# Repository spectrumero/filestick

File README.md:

# FileStick

This is still a very early work in progress.

This project implements an Econet fileserver "onna stick". Acorn had
the FileStore, so this is kind of a play on words on the FileStore.
The system is built on a Lattice UltraPlus 5K FPGA, which includes
128kbyte of static RAM on the chip, as well as a number of dual ported
blockrams, which makes it ideal for a small system project.

The prototype board is based on the UPduino 3.1 board.
See: https://tinyvision.ai/products/upduino-v3-1

The version 1 board contains the econet front end, the up5k FPGA,
an SD card slot, flash memory and a USB interface, implemented with
an FTDI USB UART.

The system consists of a RISC-V core (modified FemtoRV core supporting
some extra CSRs, the ecall instruction to handle system calls, ebreak
and some limited illegal instruction trapping). The core is an rv32imc
(RISC-V 32 bit with the multiply/divide and compressed instructions
extensions).

## Features

* USB powered, < 500mA
* Simple RISC-V implementation and early microcomputer style operating
system. System functions via `ecall` interface.
* Fully buffered econet implementation, with econet exposed via standard
open/read/write/close/ioctl operations.
* Switchable econet clock generation and termination, so that you don't
need a separate clock and terminators for a small Econet.
* Programmable timers.
* USB serial interface with hardware FIFO and hardware CTS/RTS flow control.
Has an interactive mode for use as the system console and raw mode for
transferring files over USB etc.
* FAT support using FatFS for both microSD and built-in flash.
* RGB LED, useful for showing system activity.
* C / C++ programming made easy with newlib and GCC riscv cross compiler,
and a lightweight library and specs file for system-specifics.

## Project structure

* hardware: Contains the Verilog source code. Requires a recent version
of yosys, nextpnr, and the icestorm tools. (Debian users will need to
build these from source, as Debian is still on the old arachnepnr).

* system: Contains the operating system. This isn't a multiuser/
multitasking operating system, it's an OS in the vein of a classic
home micro's operating system. It does provide a number of system
calls using the Linux rv32 syscall numbers. Remember there is no
virtual memory on this very small system, however, some simple memory
protection is planned so that user programs can't accidentally
overwrite kernel memory or device address space.

* lib: The filestick library. This is required for most userspace programs
as at the very least it provides the sbrk implementation needed to properly
support libc's malloc.

## Other programs

(Full disclosure: the emulator and BASIC interpreter below was done with the
full assistance of Claude Code, much as it would be an interesting
project to do them from scratch, it would take me far too long, I had
already been putting off writing the emulator for 2 years :-) )

* emulator: An emulator. See the README file for how to use it. The
emulator is based off the Verilog code and should match it closely.
At the moment it only supports an OS with pseudottys (e.g. Linux) but
it's probably not too hard to do a version for Windows for anyone so
inclined. By default, tries to match the running speed of the real hardware.

* basic: A small BBC BASIC implementation. Implements most of BASIC II
as you would find on a BBC Micro and should be compatible with a saved
BBC BASIC file. Graphics/sound/screen modes not implemented because 
there aren't any. Nor is there an assembler (if you want to write rv32
asm, I suggest using xpack's gnu as). The code segment is around 28k, 
and when running on the board, there's about 33k available for BASIC programs.

* cputest: A test suite for the CPU, checking each unprivileged RV32IMC
instruction against the RISC-V specification. See the README file.

## Toolchain

The xPack GNU RISC-V embedded GCC project is used to build all source
code. xPack provides ready-to-run toolchains for many platforms including
Linux, Windows and MacOS. Other GCC toolchains will probably work, but xPack
is likely the easiest/most convenient to use.

The xPack toolchain includes newlib (the libc).

See their releases here: 
https://github.com/xpack-dev-tools/riscv-none-elf-gcc-xpack/releases

The build system uses cmake. If you're running Linux, your distro almost
certainly has cmake. Otherwise see: https://cmake.org/

## Building

To build the gateware, you will need yosys, nextpnr and icestorm tools installed.
Run:

```
$ cd rtl
$ make PCF=<pcf version of your board>
```

If the PCF variable is left unset, the default will be picked which will be for the
latest version of the hardware.

To build the software, assuming a suitable rv32 compiler (e.g. the xpack one suggested):

```
$ cmake -B build
$ cd build
$ make
```

Outputs will be `build/system/filestick-system.bin`, `build/boot/filestick-boot.bin`,
`build/lib/libfilestick.a`, `build/init/init.elf`.

## Installing

To install the gateware, in the `rtl` directory run `make flash` which will use a
suitable FTDI FT232H programmer to write the flash. This also installs the bootloader
as part of the gateware file.

To install the system image with the FTDI programmer:

```
iceprog -d i:0x0403:0x6014 -X -o 0x020000 build/system/filestick-system.bin
```

To install init with the FTDI programmer:

```
iceprog -d i:0x0403:0x6014 -o 0x030000 build/init/init.elf
```

To install the in-built filesystem:

```
iceprog -d i:0x0403:0x6014 -o 0x040000 256kfs.img
```

(256kfs.img is a blank 256k fat12 filesystem, used for storing system settings
and some basic software).

## TODO

There's much to do. More to come later, including how to write programs
for the FileStick.

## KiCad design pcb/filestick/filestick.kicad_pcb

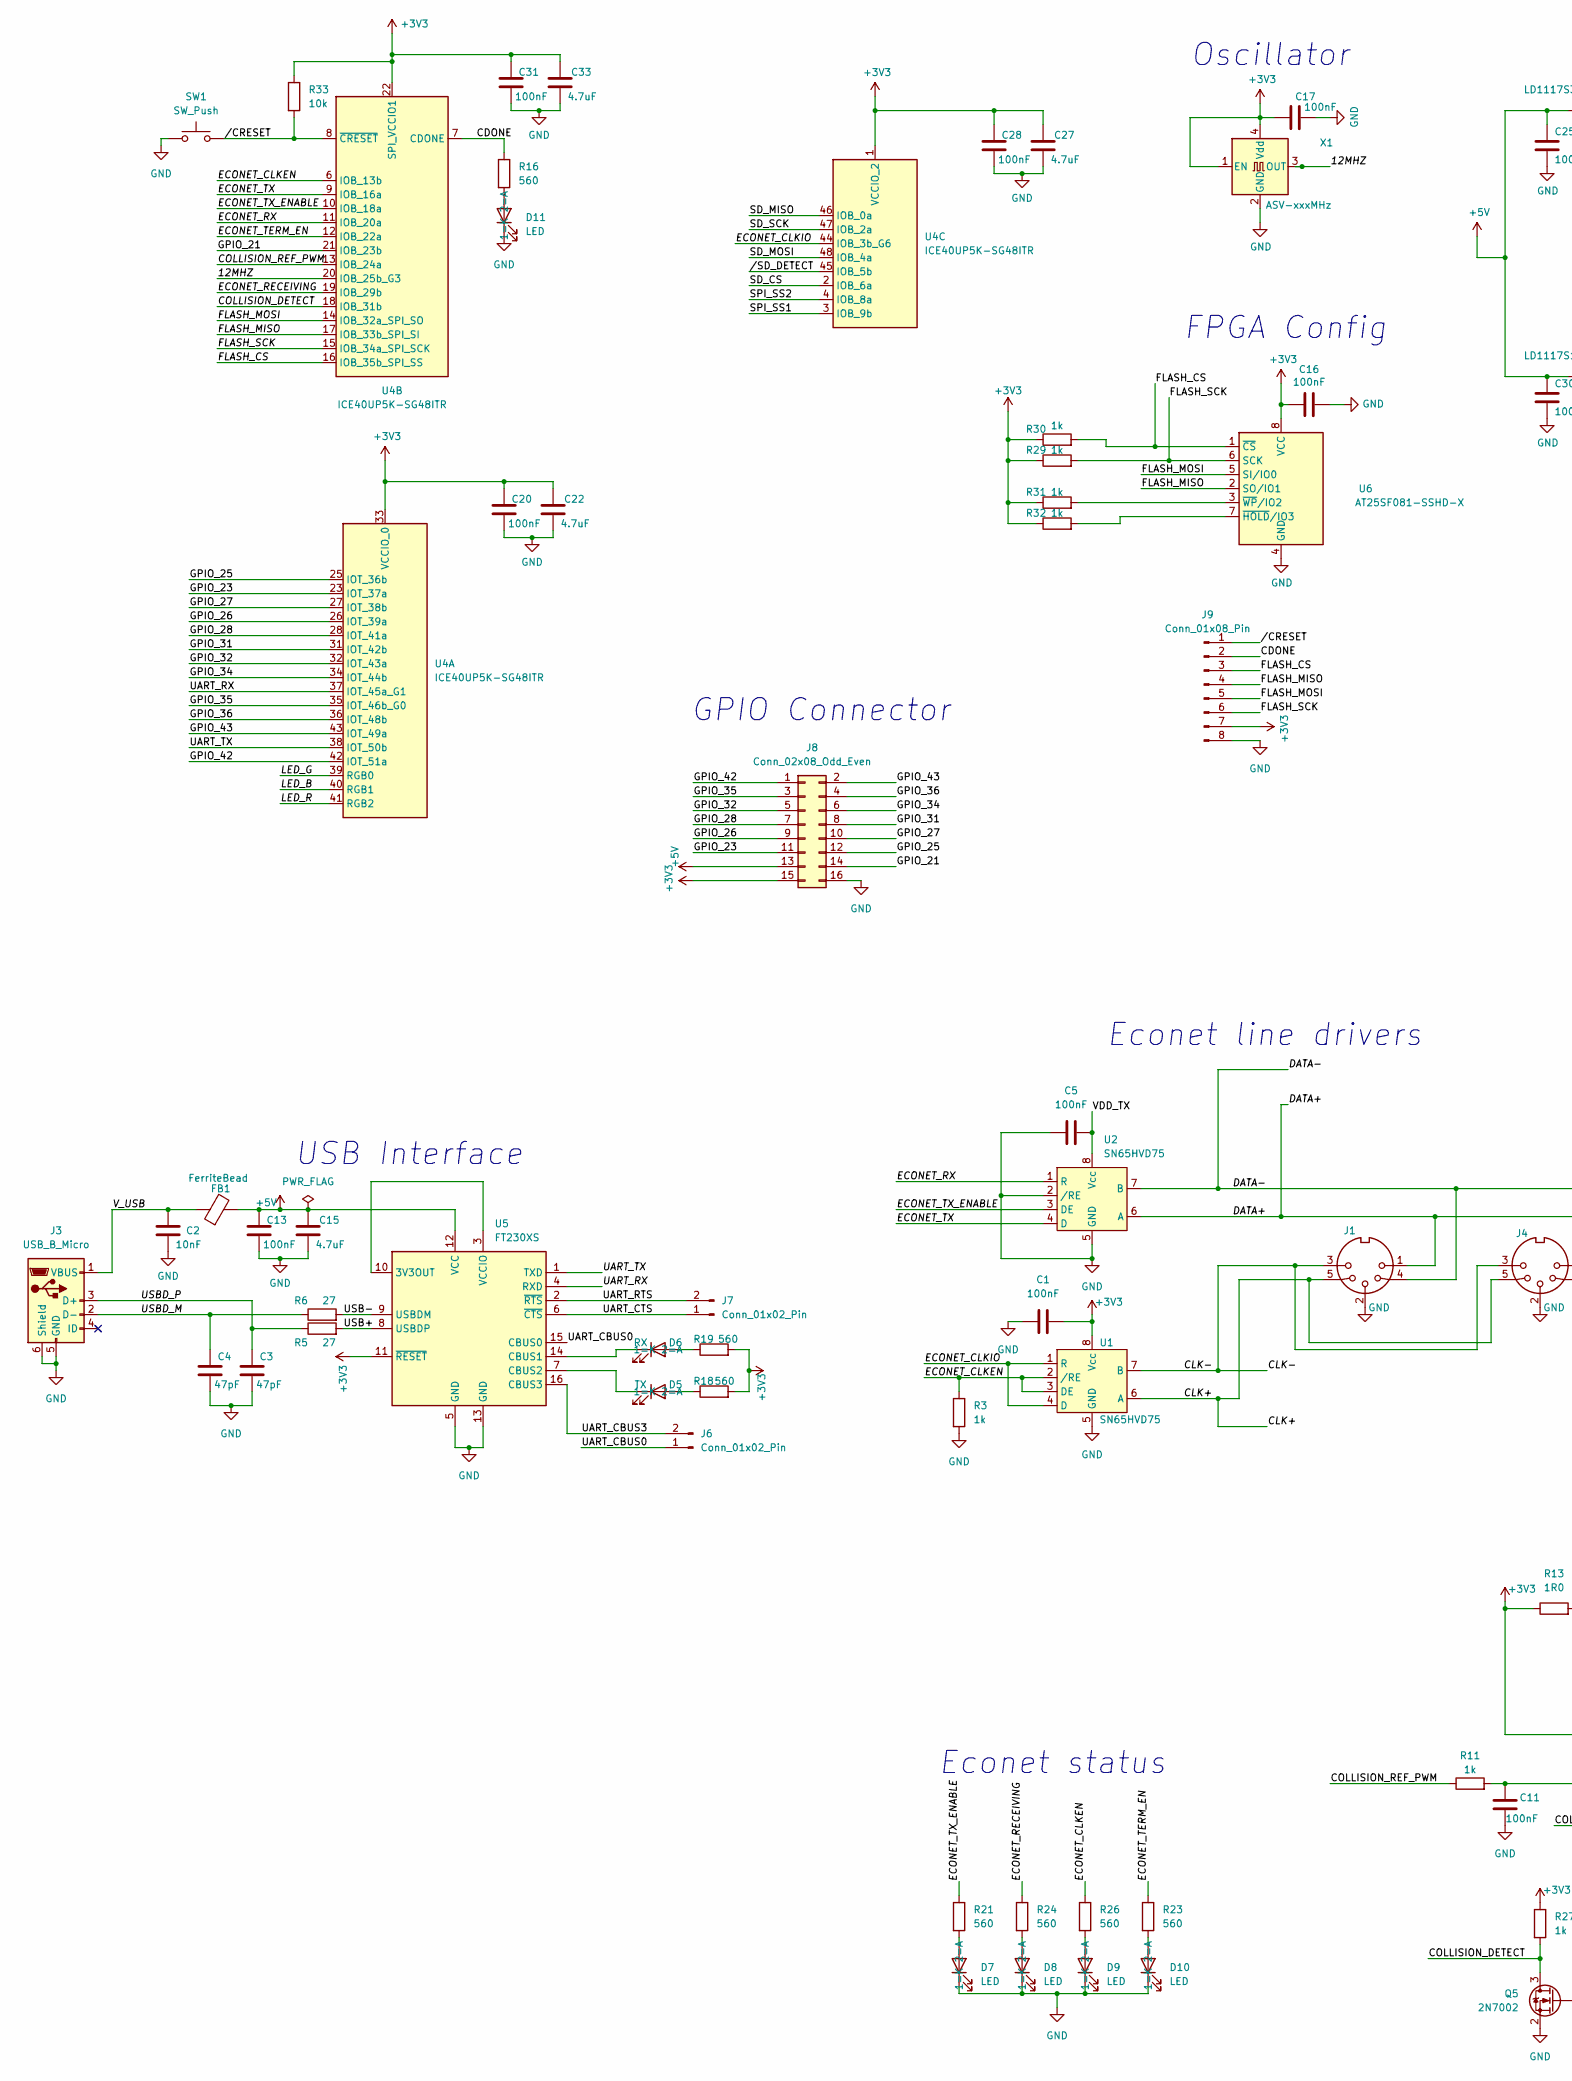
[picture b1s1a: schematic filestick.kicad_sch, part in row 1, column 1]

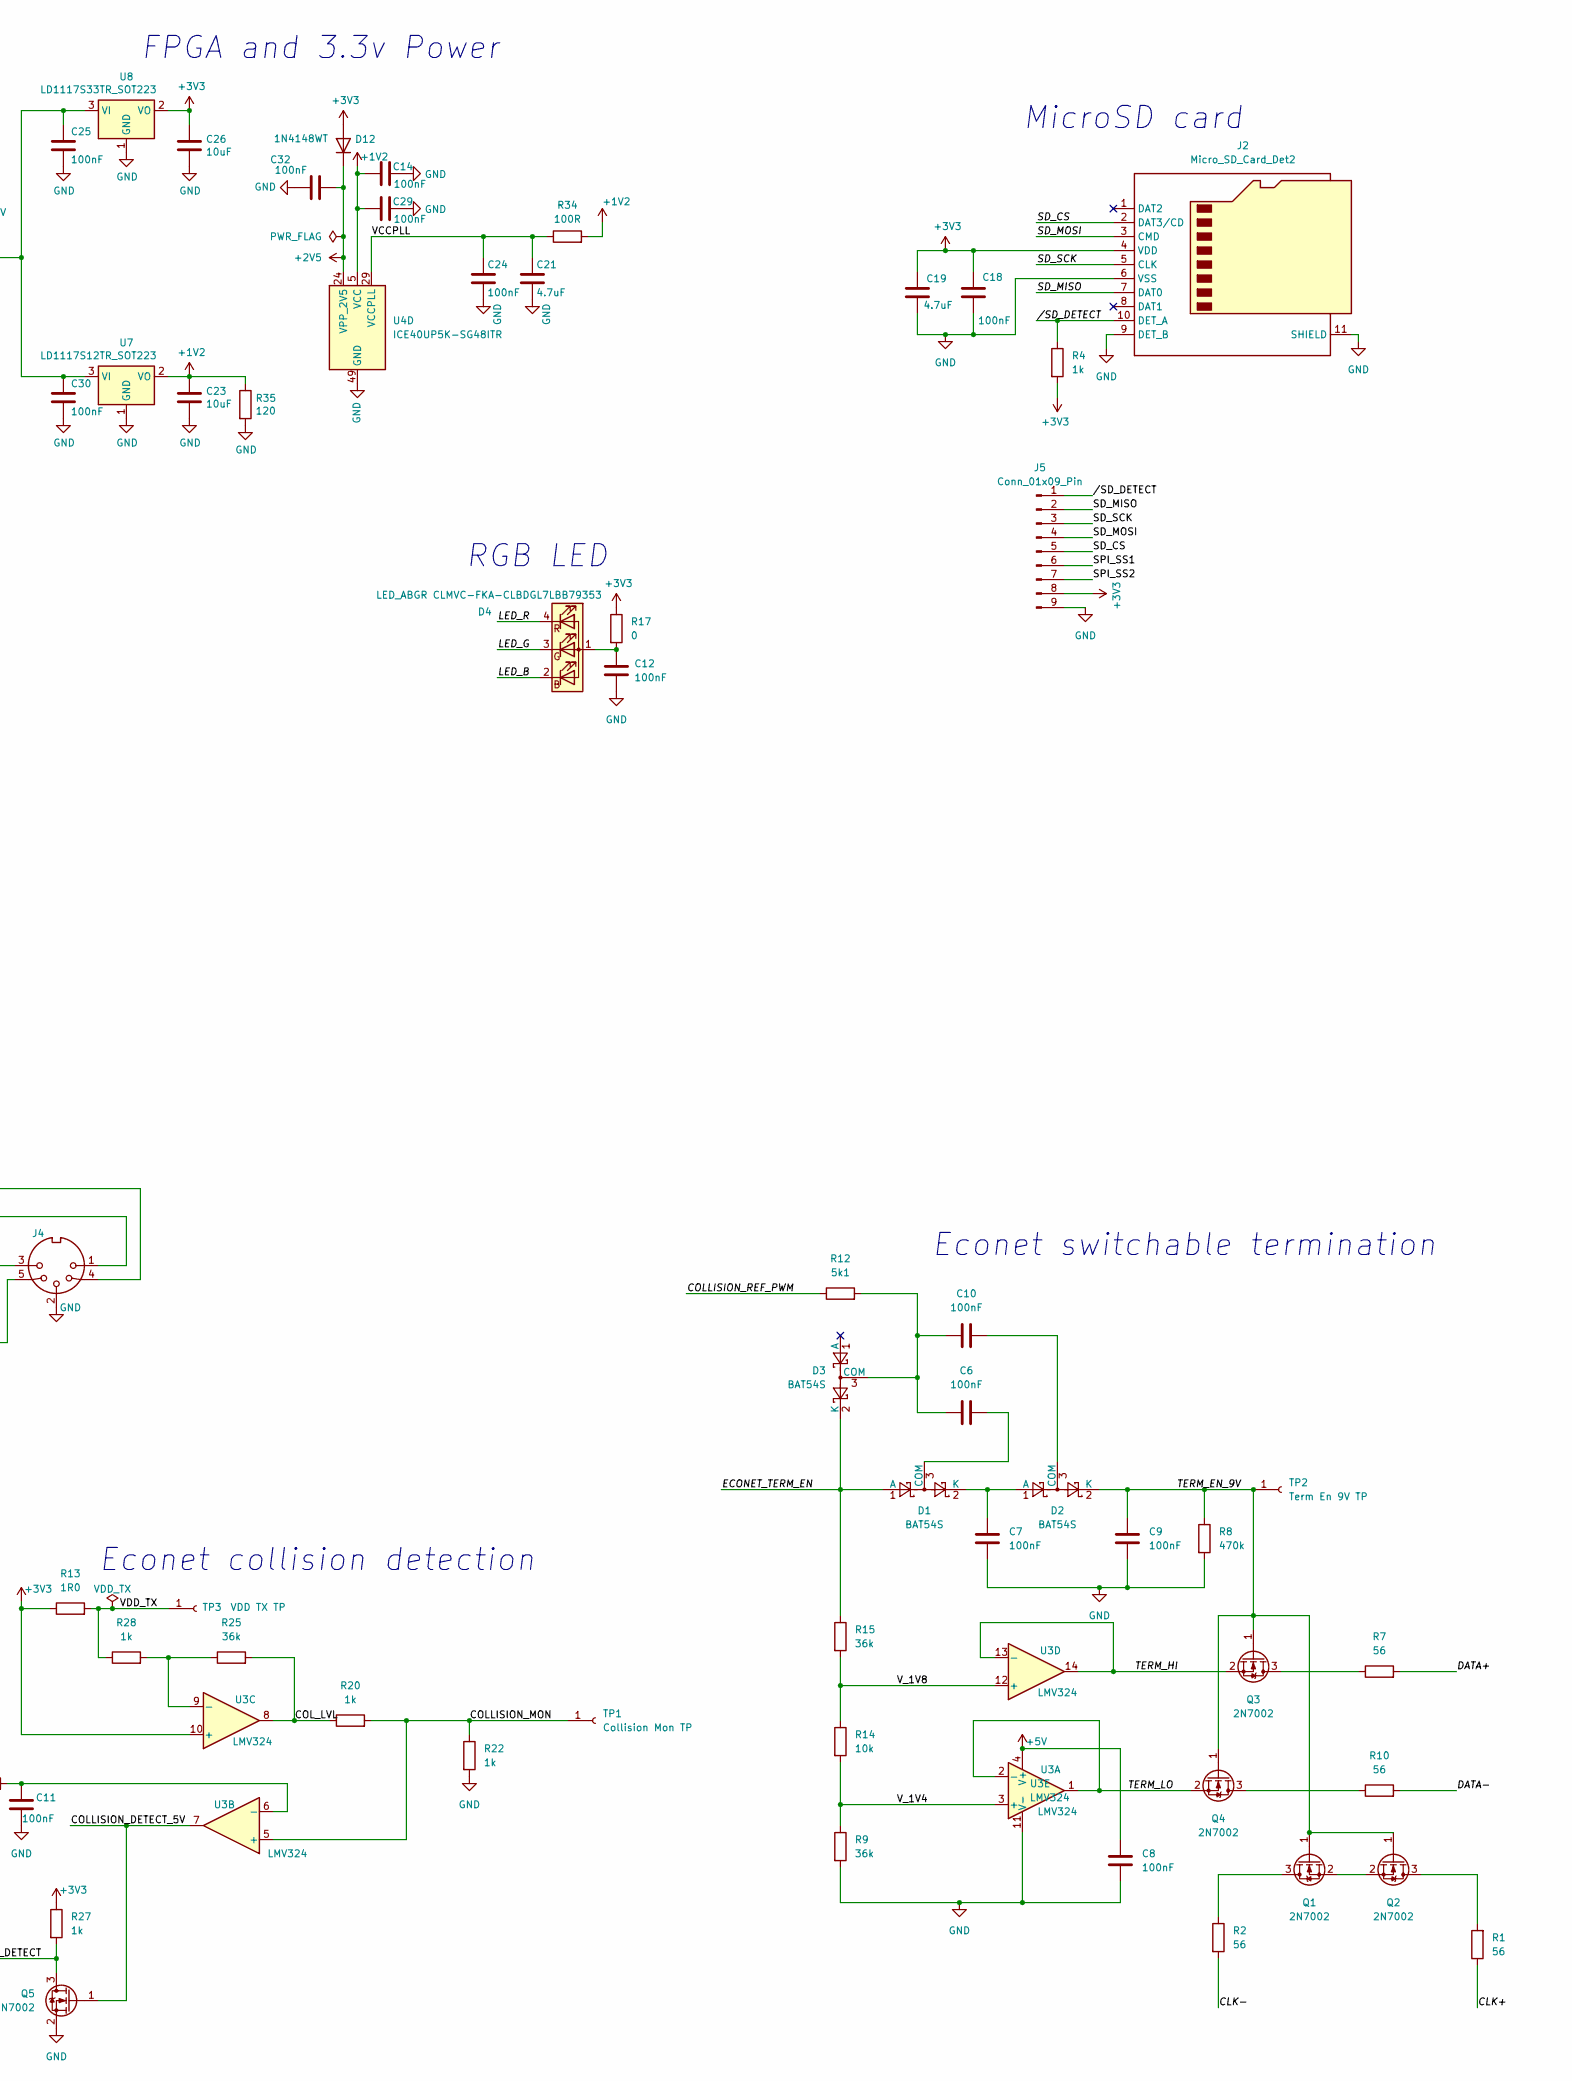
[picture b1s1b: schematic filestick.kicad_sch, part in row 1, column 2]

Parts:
C1, C5, C6, C7, C8, C9, C10, C11, C12, C13, C14, C16, C17, C18, C20, C24, C25, C28, C29, C30, C31, C32: 100nF; C_0603_1608Metric_Pad1.08x0.95mm_HandSolder
C2: 10nF; C_0603_1608Metric_Pad1.08x0.95mm_HandSolder
C3, C4: 47pF; C_0603_1608Metric_Pad1.08x0.95mm_HandSolder
C15, C19, C21, C22, C27, C33: 4.7uF; C_0603_1608Metric_Pad1.08x0.95mm_HandSolder
C23, C26: 10uF; C_0603_1608Metric_Pad1.08x0.95mm_HandSolder
D1, D2, D3: BAT54S; SOT-23
D4: LED_ABGR CLMVC-FKA-CLBDGL7LBB79353; LED_Cree-PLCC4_2x2mm_CW
D5: TX; LED_0603_1608Metric_Pad1.05x0.95mm_HandSolder
D6: RX; LED_0603_1608Metric_Pad1.05x0.95mm_HandSolder
D7, D8, D9, D10, D11: LED; LED_0603_1608Metric_Pad1.05x0.95mm_HandSolder
D12: 1N4148WT; D_SOD-523
FB1: FerriteBead; L_0603_1608Metric_Pad1.05x0.95mm_HandSolder
J1, J4: DIN-5_180degree; Lumberg_DIN41524_5pin
J2: Micro_SD_Card_Det2; microSD_HC_Hirose_DM3D-SF
J3: USB_B_Micro; USB_Micro-B_Molex-105017-0001
J5: Conn_01x09_Pin; PinHeader_1x09_P2.54mm_Vertical
J6, J7: Conn_01x02_Pin; PinHeader_1x02_P2.54mm_Vertical
J8: Conn_02x08_Odd_Even; PinHeader_2x08_P2.54mm_Vertical
J9: Conn_01x08_Pin; PinHeader_1x08_P2.54mm_Vertical
Q1, Q2, Q3, Q4, Q5: 2N7002; SOT-23
R1, R2, R7, R10: 56; R_0603_1608Metric_Pad0.98x0.95mm_HandSolder
R3, R4, R11, R20, R22, R27, R28, R29, R30, R31, R32: 1k; R_0603_1608Metric_Pad0.98x0.95mm_HandSolder
R5, R6: 27; R_0603_1608Metric_Pad0.98x0.95mm_HandSolder
R8: 470k; R_0603_1608Metric_Pad0.98x0.95mm_HandSolder
R9, R15, R25: 36k; R_0603_1608Metric_Pad0.98x0.95mm_HandSolder
R12: 5k1; R_0603_1608Metric_Pad0.98x0.95mm_HandSolder
R13: 1R0; R_0603_1608Metric_Pad0.98x0.95mm_HandSolder
R14, R33: 10k; R_0603_1608Metric_Pad0.98x0.95mm_HandSolder
R16, R18, R19, R21, R23, R24, R26: 560; R_0603_1608Metric_Pad0.98x0.95mm_HandSolder
R17: 0; R_0603_1608Metric_Pad0.98x0.95mm_HandSolder
R34: 100R; R_0603_1608Metric_Pad0.98x0.95mm_HandSolder
R35: 120; R_0603_1608Metric_Pad0.98x0.95mm_HandSolder
SW1: SW_Push; SW_SPST_PTS645
TP1: Collision Mon TP; PinHeader_1x01_P2.54mm_Vertical
TP2: Term En 9V TP; PinHeader_1x01_P2.54mm_Vertical
TP3: VDD TX TP; PinHeader_1x01_P2.54mm_Vertical
U1, U2: SN65HVD75; SOIC-8_5.3x6.2mm_P1.27mm
U3: LMV324; SO-14_5.3x10.2mm_P1.27mm
U4: ICE40UP5K-SG48ITR; QFN-48-1EP_7x7mm_P0.5mm_EP5.6x5.6mm
U5: FT230XS; SSOP-16_3.9x4.9mm_P0.635mm
U6: AT25SF081-SSHD-X; SOIC-8_3.9x4.9mm_P1.27mm
U7: LD1117S12TR_SOT223; SOT-223-3_TabPin2
U8: LD1117S33TR_SOT223; SOT-223-3_TabPin2
X1: ASV-xxxMHz; Oscillator_SMD_Abracon_ASV-4Pin_7.0x5.1mm

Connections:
+1V2: C14.2, C23.1, C29.2, R34.2, R35.1, U4.5 (VCC), U4.30 (VCC), U7.2 (VO)
+2V5: C32.1, D12.1 (K), U4.24 (VPP_2V5)
+3V3: C1.1, C16.1, C17.1, C18.1, C19.1, C20.2, C22.2, C26.1, C27.2, C28.2, C31.2, C33.2, D12.2 (A), J2.4 (VDD), J5.8, J8.15, J9.7, R4.2, R13.1, R17.1, R18.2, R19.2, R27.1, R29.1, R30.1, R31.1, R32.1, R33.1, U1.8 (Vcc), U3.10 (+), U4.1 (VCCIO_2), U4.22 (SPI_VCCIO1), U4.33 (VCCIO_0), U5.11 (~RESET), U6.8 (VCC), U8.2 (VO), X1.1 (EN), X1.4 (Vdd)
+5V: C8.1, C13.2, C15.2, C25.1, C30.1, FB1.2, J8.13, U3.4 (V+), U5.12 (VCC), U7.3 (VI), U8.3 (VI)
/12MHZ: U4.20 (IOB_25b_G3), X1.3 (OUT)
/CDONE: J9.2, R16.1, U4.7 (CDONE)
/CLK+: J1.5, J4.5, R1.1, U1.6 (A)
/CLK-: J1.3, J4.3, R2.2, U1.7 (B)
/COLLISION_DETECT: Q5.3 (D), R27.2, U4.18 (IOB_31b)
/COLLISION_DETECT_5V: Q5.1 (G), U3.7
/COLLISION_MON: R20.2, R22.1, TP1.1, U3.5 (+)
/COLLISION_REF_PWM: R11.1, R12.1, U4.13 (IOB_24a)
/COL_LVL: R20.1, R25.2, U3.8
/DATA+: J1.1, J4.1, R7.2, U2.6 (A)
/DATA-: J1.4, J4.4, R10.2, U2.7 (B)
/ECONET_CLKEN: R3.1, R26.1, U1.2 (/RE), U1.3 (DE), U4.6 (IOB_13b)
/ECONET_CLKIO: U1.1 (R), U1.4 (D), U4.44 (IOB_3b_G6)
/ECONET_RECEIVING: R24.1, U4.19 (IOB_29b)
/ECONET_RX: U2.1 (R), U4.11 (IOB_20a)
/ECONET_TERM_EN: D1.1 (A), D3.2 (K), R15.1, R23.1, U4.12 (IOB_22a)
/ECONET_TX: U2.4 (D), U4.9 (IOB_16a)
/ECONET_TX_ENABLE: R21.1, U2.3 (DE), U4.10 (IOB_18a)
/FLASH_CS: J9.3, R30.2, U4.16 (IOB_35b_SPI_SS), U6.1 (~CS)
/FLASH_MISO: J9.4, U4.17 (IOB_33b_SPI_SI), U6.2 (SO/IO1)
/FLASH_MOSI: J9.5, U4.14 (IOB_32a_SPI_SO), U6.5 (SI/IO0)
/FLASH_SCK: J9.6, R29.2, U4.15 (IOB_34a_SPI_SCK), U6.6 (SCK)
/GPIO_21: J8.14, U4.21 (IOB_23b)
/GPIO_23: J8.11, U4.23 (IOT_37a)
/GPIO_25: J8.12, U4.25 (IOT_36b)
/GPIO_26: J8.9, U4.26 (IOT_39a)
/GPIO_27: J8.10, U4.27 (IOT_38b)
/GPIO_28: J8.7, U4.28 (IOT_41a)
/GPIO_31: J8.8, U4.31 (IOT_42b)
/GPIO_32: J8.5, U4.32 (IOT_43a)
/GPIO_34: J8.6, U4.34 (IOT_44b)
/GPIO_35: J8.3, U4.35 (IOT_46b_G0)
/GPIO_36: J8.4, U4.36 (IOT_48b)
/GPIO_42: J8.1, U4.42 (IOT_51a)
/GPIO_43: J8.2, U4.43 (IOT_49a)
/LED_B: D4.2 (BK), U4.40 (RGB1)
/LED_G: D4.3 (GK), U4.39 (RGB0)
/LED_R: D4.4 (RK), U4.41 (RGB2)
/SD_CS: J2.2 (DAT3/CD), J5.5, U4.2 (IOB_6a)
/SD_MISO: J2.7 (DAT0), J5.2, U4.46 (IOB_0a)
/SD_MOSI: J2.3 (CMD), J5.4, U4.48 (IOB_4a)
/SD_SCK: J2.5 (CLK), J5.3, U4.47 (IOB_2a)
/SPI_SS1: J5.6, U4.3 (IOB_9b)
/SPI_SS2: J5.7, U4.4 (IOB_8a)
/TERM_EN_9V: C9.1, D2.2 (K), Q1.1 (G), Q2.1 (G), Q3.1 (G), Q4.1 (G), R8.1, TP2.1
/TERM_HI: Q3.2 (S), U3.13 (-), U3.14
/TERM_LO: Q4.2 (S), U3.1, U3.2 (-)
/UART_CBUS0: J6.1, U5.15 (CBUS0)
/UART_CBUS3: J6.2, U5.16 (CBUS3)
/UART_CTS: J7.1, U5.6 (~CTS)
/UART_RTS: J7.2, U5.2 (~RTS)
/UART_RX: U4.37 (IOT_45a_G1), U5.4 (RXD)
/UART_TX: U4.38 (IOT_50b), U5.1 (TXD)
/USB+: R5.2, U5.8 (USBDP)
/USB-: R6.2, U5.9 (USBDM)
/USBD_M: C4.1, J3.2 (D-), R6.1
/USBD_P: C3.1, J3.3 (D+), R5.1
/VCCPLL: C21.1, C24.1, R34.1, U4.29 (VCCPLL)
/VDD_TX: C5.2, R13.2, R28.1, TP3.1, U2.8 (Vcc)
/V_1V4: R9.1, R14.2, U3.3 (+)
/V_1V8: R14.1, R15.2, U3.12 (+)
/V_USB: C2.1, FB1.1, J3.1 (VBUS)
//CRESET: J9.1, R33.2, SW1.2, U4.8 (~CRESET)
//SD_DETECT: J2.10 (DET_A), J5.1, R4.1, U4.45 (IOB_5b)
GND: C1.2, C2.2, C3.2, C4.2, C5.1, C7.2, C8.2, C9.2, C11.2, C12.2, C13.1, C14.1, C15.1, C16.2, C17.2, C18.2, C19.2, C20.1, C21.2, C22.1, C23.2, C24.2, C25.2, C26.2, C27.1, C28.1, C29.1, C30.2, C31.1, C32.2, C33.1, D7.1 (K), D8.1 (K), D9.1 (K), D10.1 (K), D11.1 (K), J1.2, J2.6 (VSS), J2.9 (DET_B), J2.11 (SHIELD), J3.5 (GND), J3.6 (Shield), J4.2, J5.9, J8.16, J9.8, Q5.2 (S), R3.2, R8.2, R9.2, R22.2, R35.2, SW1.1, U1.5 (GND), U2.2 (/RE), U2.5 (GND), U3.11 (V-), U4.49 (GND), U5.5 (GND), U5.13 (GND), U6.4 (GND), U7.1 (GND), U8.1 (GND), X1.2 (GND)
unnamed: C6.2, D1.3 (COM)
unnamed: C7.1, D1.2 (K), D2.1 (A)
unnamed: C10.2, D2.3 (COM)
unnamed: C6.1, C10.1, D3.3 (COM), R12.2
unnamed: C12.1, D4.1 (A), R17.2
unnamed: D5.2 (A), R18.1
unnamed: D5.1 (K), U5.7 (CBUS2)
unnamed: D6.2 (A), R19.1
unnamed: D6.1 (K), U5.14 (CBUS1)
unnamed: D7.2 (A), R21.2
unnamed: D8.2 (A), R24.2
unnamed: D9.2 (A), R26.2
unnamed: D10.2 (A), R23.2
unnamed: D11.2 (A), R16.2
unnamed: Q1.3 (D), R2.1
unnamed: Q1.2 (S), Q2.2 (S)
unnamed: Q2.3 (D), R1.2
unnamed: Q3.3 (D), R7.1
unnamed: Q4.3 (D), R10.1
unnamed: C11.1, R11.2, U3.6 (-)
unnamed: R25.1, R28.2, U3.9 (-)
unnamed: U5.3 (VCCIO), U5.10 (3V3OUT)
unnamed: R32.2, U6.7 (~HOLD/IO3)
unnamed: R31.2, U6.3 (~WP/IO2)

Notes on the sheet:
GPIO Connector
MicroSD card
Econet switchable termination
RGB LED
FPGA and 3.3v Power
Econet status
Econet line drivers
Oscillator
FPGA Config
USB Interface
Econet collision detection

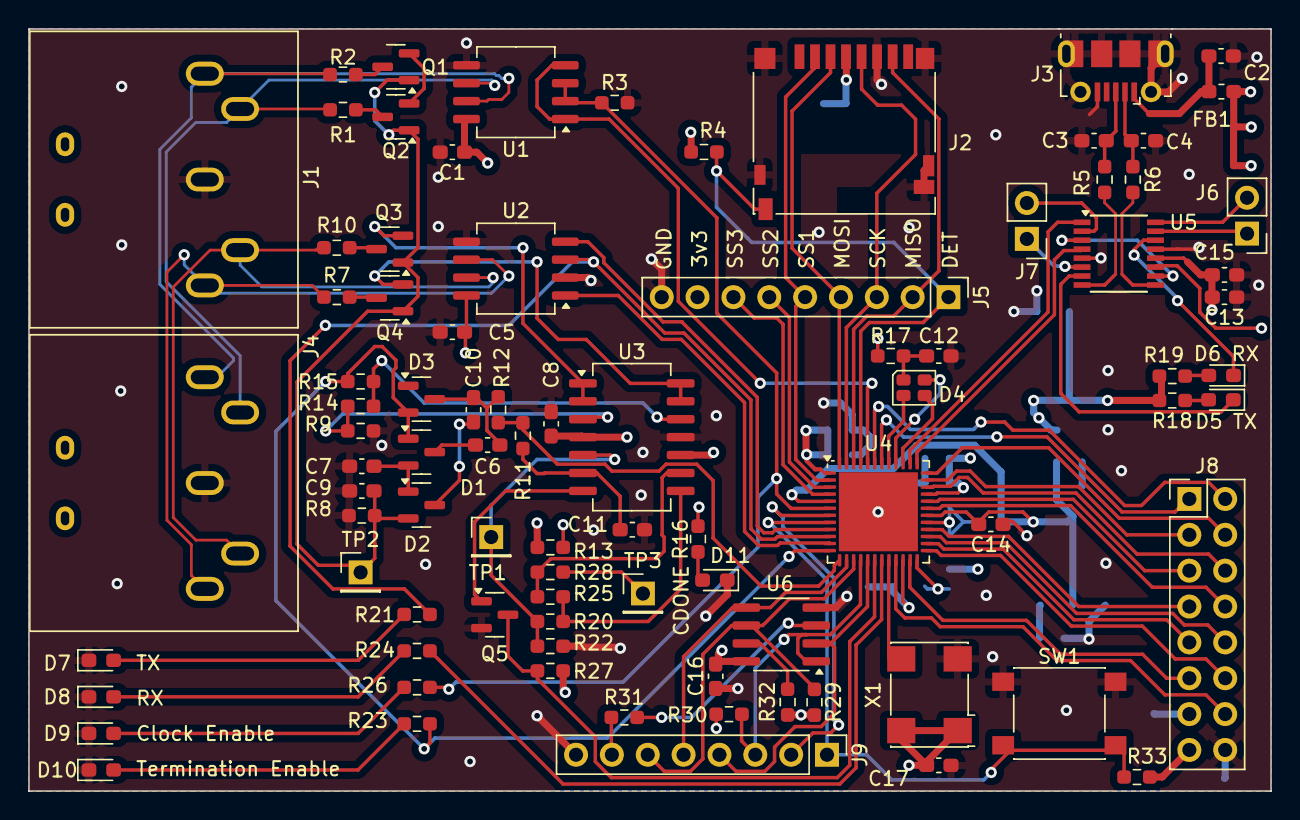
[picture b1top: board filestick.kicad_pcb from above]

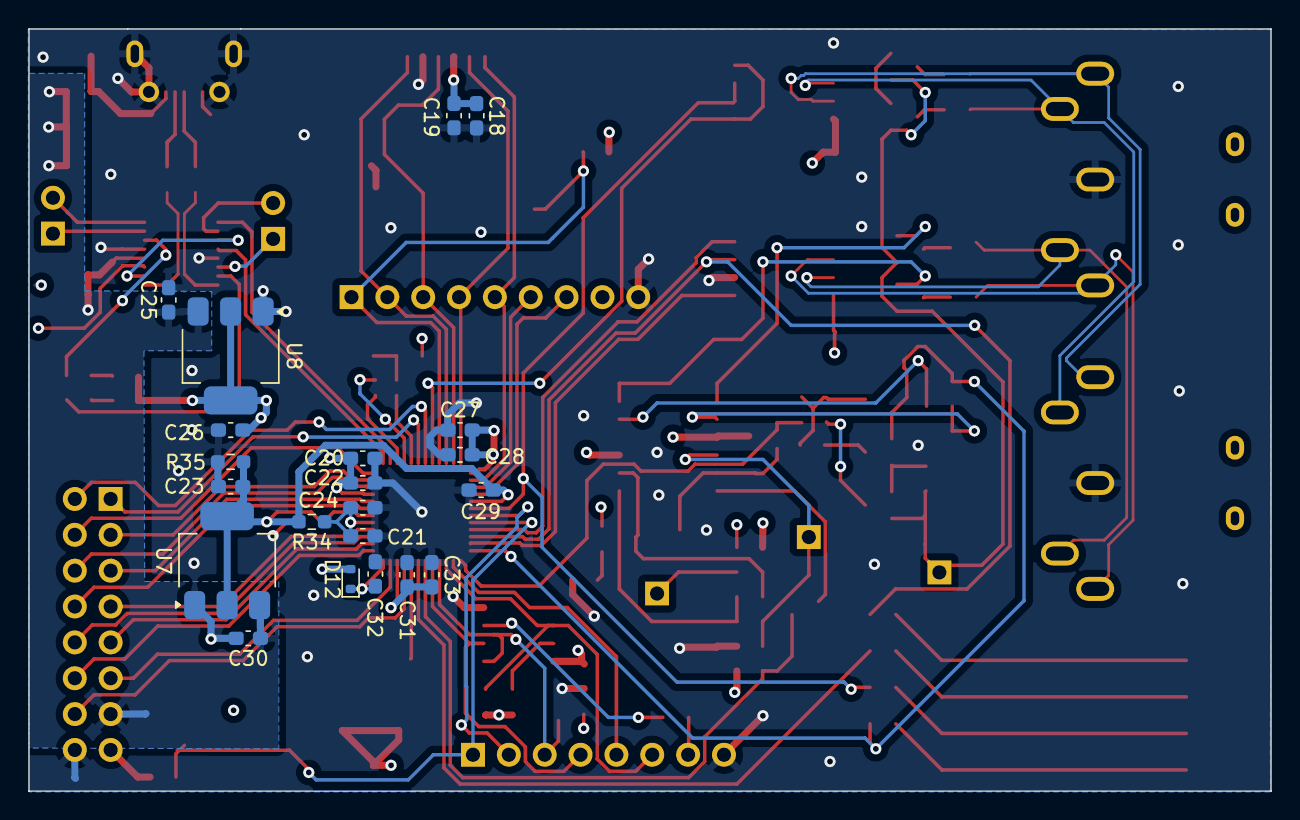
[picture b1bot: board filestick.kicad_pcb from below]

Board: 4 copper layers, 88.0 x 54.0 mm, 108 parts (21 on the bottom side), 93 nets.

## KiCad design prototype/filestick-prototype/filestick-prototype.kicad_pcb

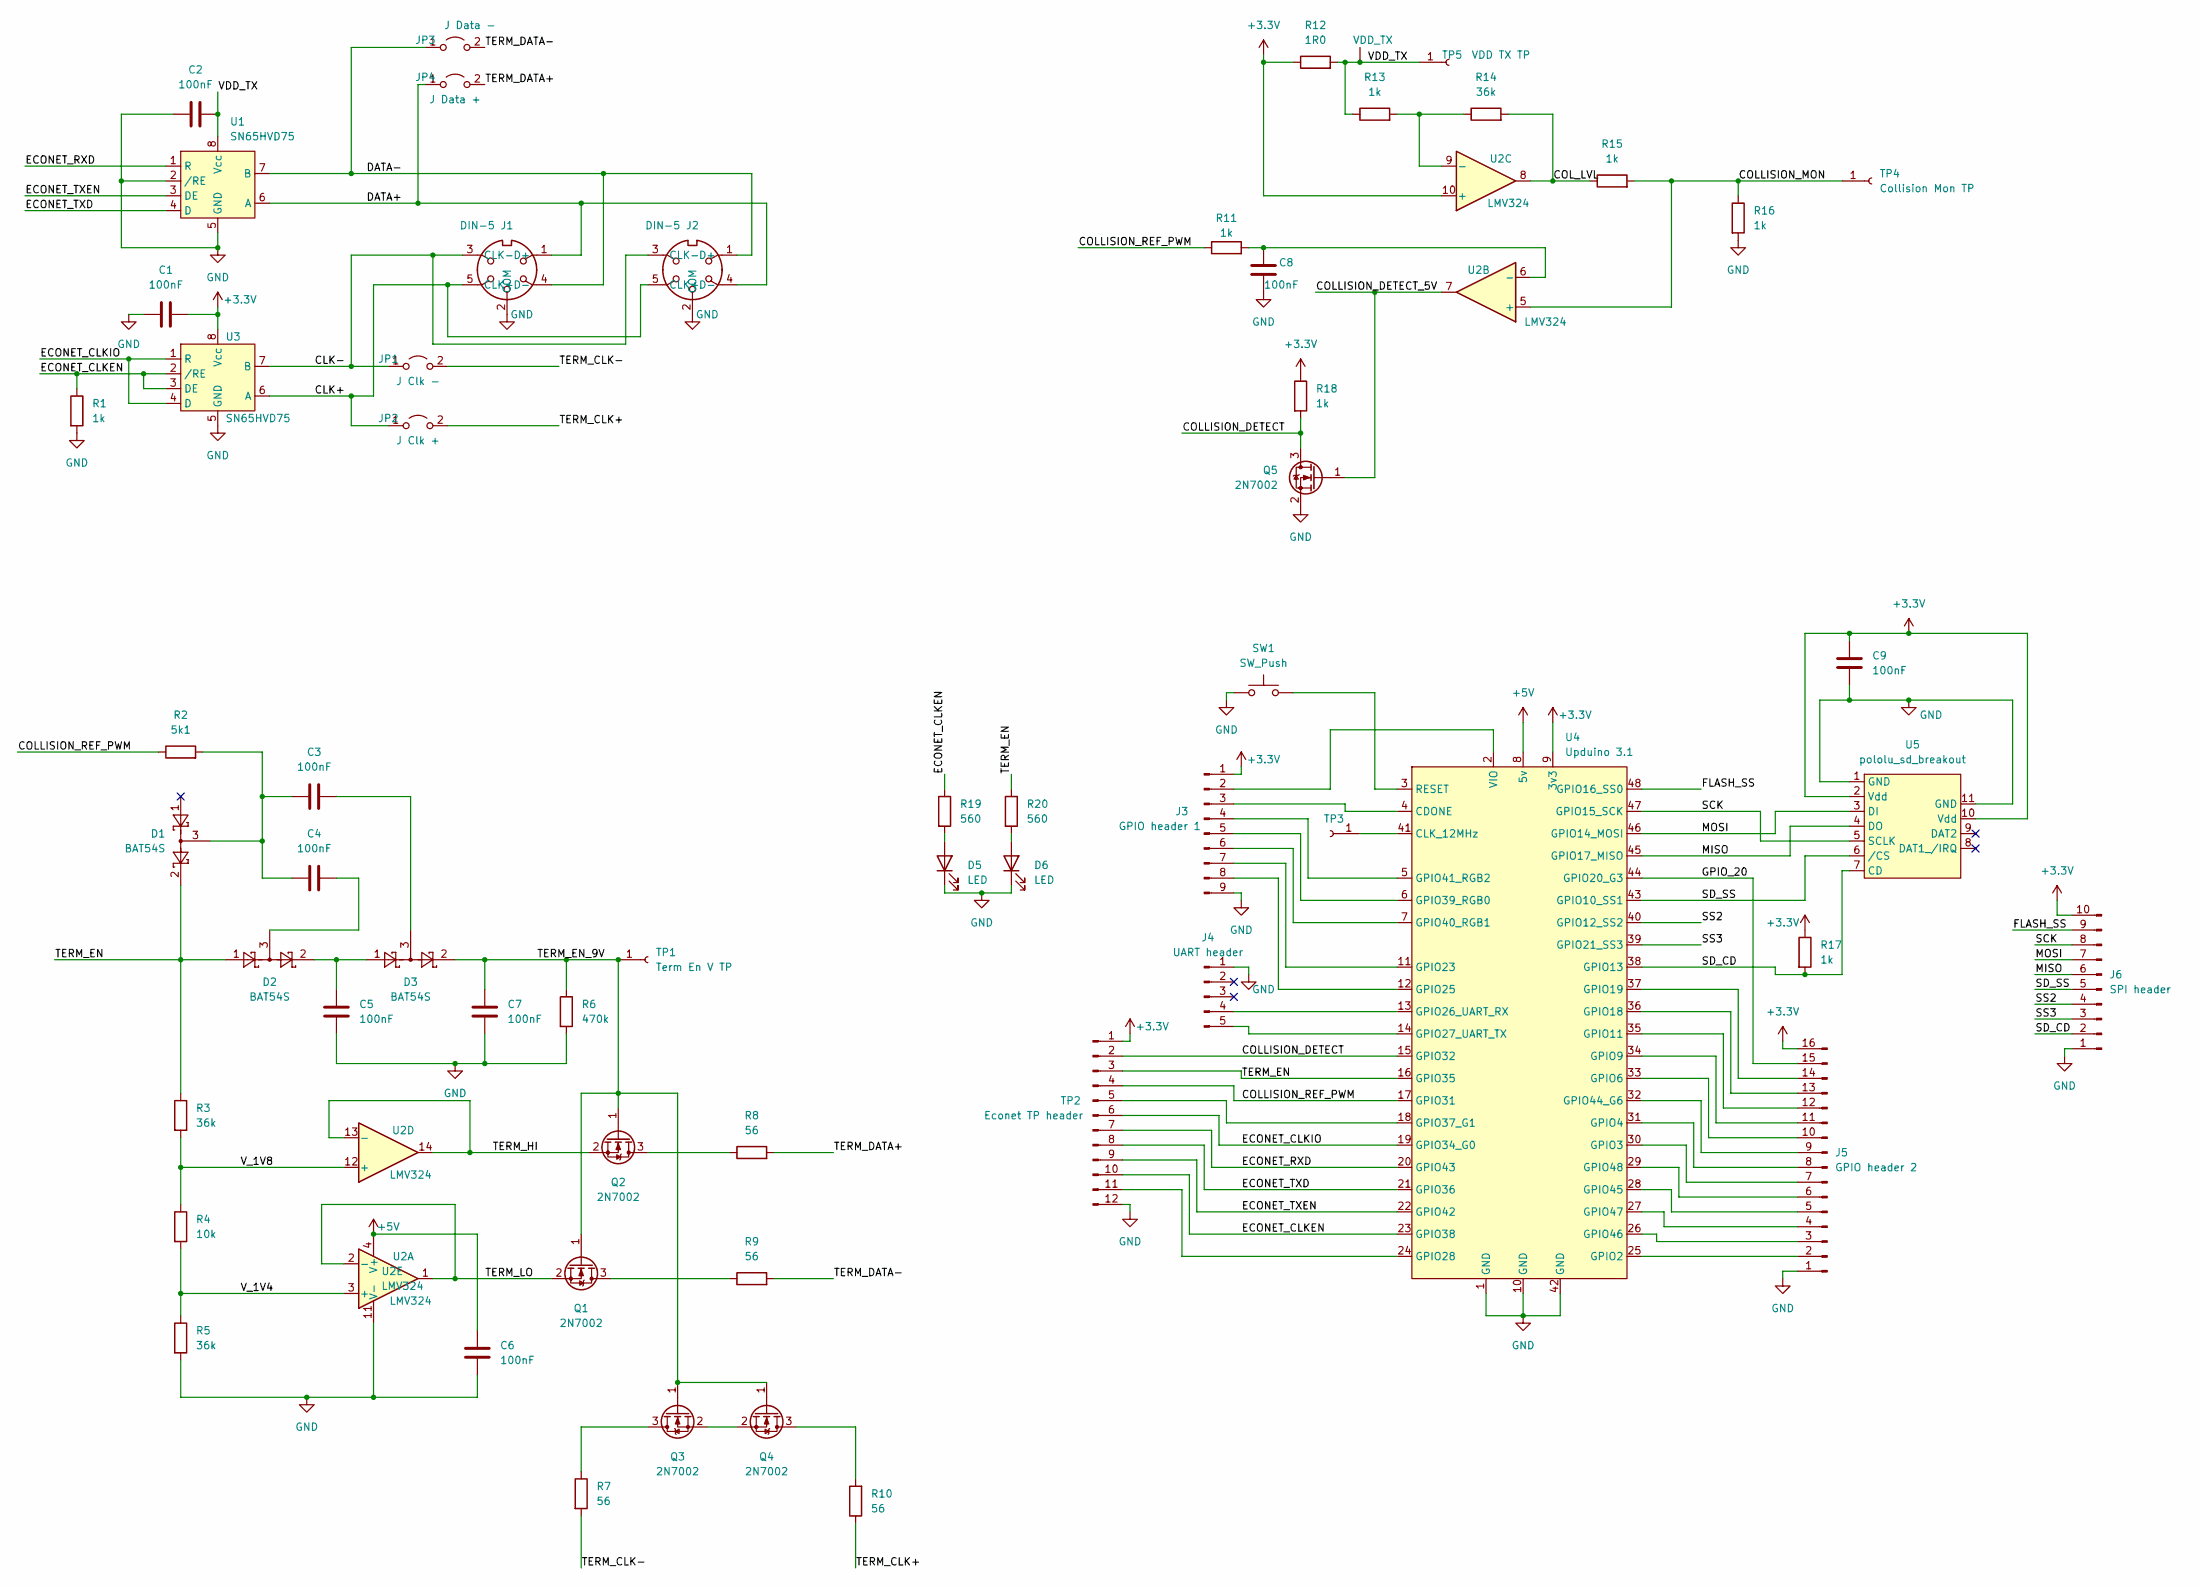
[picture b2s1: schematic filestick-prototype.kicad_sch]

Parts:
C1, C2, C3, C4, C5, C6, C7, C8, C9: 100nF; C_0603_1608Metric_Pad1.08x0.95mm_HandSolder
D1, D2, D3: BAT54S; SOT-23
D5, D6: LED; LED_0603_1608Metric_Pad1.05x0.95mm_HandSolder
J1, J2: DIN-5; Lumberg_DIN41524_5pin
J3: GPIO header 1; PinHeader_1x09_P2.54mm_Vertical
J4: UART header; PinHeader_1x05_P2.54mm_Vertical
J5: GPIO header 2; PinHeader_1x16_P2.54mm_Vertical
J6: SPI header; PinHeader_1x10_P2.54mm_Vertical
JP1: J Clk -; PinHeader_1x02_P2.54mm_Vertical
JP2: J Clk +; PinHeader_1x02_P2.54mm_Vertical
JP3: J Data -; PinHeader_1x02_P2.54mm_Vertical
JP4: J Data +; PinHeader_1x02_P2.54mm_Vertical
Q1, Q2, Q3, Q4, Q5: 2N7002; SOT-23
R1, R11, R13, R15, R16, R17, R18: 1k; R_0603_1608Metric_Pad0.98x0.95mm_HandSolder
R2: 5k1; R_0603_1608Metric_Pad0.98x0.95mm_HandSolder
R3, R5, R14: 36k; R_0603_1608Metric_Pad0.98x0.95mm_HandSolder
R4: 10k; R_0603_1608Metric_Pad0.98x0.95mm_HandSolder
R6: 470k; R_0603_1608Metric_Pad0.98x0.95mm_HandSolder
R7, R8, R9, R10: 56; R_0603_1608Metric_Pad0.98x0.95mm_HandSolder
R12: 1R0; R_0603_1608Metric_Pad0.98x0.95mm_HandSolder
R19, R20: 560; R_0603_1608Metric_Pad0.98x0.95mm_HandSolder
SW1: SW_Push; SW_Push_1P1T_NO_6x6mm_H9.5mm
TP1: Term En V TP; PinHeader_1x01_P2.54mm_Vertical
TP2: Econet TP header; PinHeader_1x12_P2.54mm_Vertical
TP3: Conn_01x01_Female; PinHeader_1x01_P2.54mm_Vertical
TP4: Collision Mon TP; PinHeader_1x01_P2.54mm_Vertical
TP5: VDD TX TP; PinHeader_1x01_P2.54mm_Vertical
U1, U3: SN65HVD75; SO-8_5.3x6.2mm_P1.27mm
U2: LMV324; SO-14_5.3x10.2mm_P1.27mm
U4: Upduino 3.1; DIP48_0.7in
U5: pololu_sd_breakout; pololu_sd_card

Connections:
+3.3V: C1.1, C9.1, J3.1, J5.16, J6.10, R12.1, R17.1, R18.1, TP2.1, U2.10 (+), U3.8 (Vcc), U4.9 (3v3), U5.2 (Vdd), U5.10 (Vdd)
+5V: C6.1, U2.4 (V+), U4.8 (5v)
/CLK+: J1.5 (CLK+), J2.5 (CLK+), JP2.1 (A), U3.6 (A)
/CLK-: J1.3 (CLK-), J2.3 (CLK-), JP1.1 (A), U3.7 (B)
/COLLISION_DETECT: Q5.3 (D), R18.2, TP2.2, U4.15 (GPIO32)
/COLLISION_DETECT_5V: Q5.1 (G), U2.7
/COLLISION_MON: R15.2, R16.1, TP4.1, U2.5 (+)
/COLLISION_REF_PWM: R2.1, R11.1, TP2.4, U4.17 (GPIO31)
/COL_LVL: R14.2, R15.1, U2.8
/DATA+: J1.1 (D+), J2.4 (D-), JP4.1 (A), U1.6 (A)
/DATA-: J1.4 (D-), J2.1 (D+), JP3.1 (A), U1.7 (B)
/ECONET_CLKEN: R1.1, R19.1, TP2.10, U3.2 (/RE), U3.3 (DE), U4.23 (GPIO38)
/ECONET_CLKIO: TP2.6, U3.1 (R), U3.4 (D), U4.19 (GPIO34_G0)
/ECONET_RXD: TP2.7, U1.1 (R), U4.20 (GPIO43)
/ECONET_TXD: TP2.8, U1.4 (D), U4.21 (GPIO36)
/ECONET_TXEN: TP2.9, U1.3 (DE), U4.22 (GPIO42)
/FLASH_SS: J6.9, U4.48 (GPIO16_SS0)
/GPIO_20: J5.15, U4.44 (GPIO20_G3)
/MISO: J6.6, U4.45 (GPIO17_MISO), U5.4 (DO)
/MOSI: J6.7, U4.46 (GPIO14_MOSI), U5.3 (DI)
/SCK: J6.8, U4.47 (GPIO15_SCK), U5.5 (SCLK)
/SD_CD: J6.2, R17.2, U4.38 (GPIO13), U5.7 (CD)
/SD_SS: J6.5, U4.43 (GPIO10_SS1), U5.6 (/CS)
/SS2: J6.4, U4.40 (GPIO12_SS2)
/SS3: J6.3, U4.39 (GPIO21_SS3)
/TERM_CLK+: JP2.2 (B), R10.1
/TERM_CLK-: JP1.2 (B), R7.2
/TERM_DATA+: JP4.2 (B), R8.2
/TERM_DATA-: JP3.2 (B), R9.2
/TERM_EN: D1.2, D2.1, R3.1, R20.1, TP2.3, U4.16 (GPIO35)
/TERM_EN_9V: C7.1, D3.2, Q1.1 (G), Q2.1 (G), Q3.1 (G), Q4.1 (G), R6.1, TP1.1
/TERM_HI: Q2.2 (S), U2.13 (-), U2.14
/TERM_LO: Q1.2 (S), U2.1, U2.2 (-)
/VDD_TX: C2.2, R12.2, R13.1, TP5.1, U1.8 (Vcc)
/V_1V4: R4.2, R5.1, U2.3 (+)
/V_1V8: R3.2, R4.1, U2.12 (+)
GND: C1.2, C2.1, C5.2, C6.2, C7.2, C8.2, C9.2, D5.1 (K), D6.1 (K), J1.2 (COM), J2.2 (COM), J3.9, J4.1, J5.1, J6.1, Q5.2 (S), R1.2, R5.2, R6.2, R16.2, SW1.1, TP2.12, U1.2 (/RE), U1.5 (GND), U2.11 (V-), U3.5 (GND), U4.1 (GND), U4.10 (GND), U4.42 (GND), U5.1 (GND), U5.11 (GND)
unnamed: C3.1, C4.1, D1.3, R2.2
unnamed: C3.2, D3.3
unnamed: C4.2, D2.3
unnamed: C5.1, D2.2, D3.1
unnamed: C8.1, R11.2, U2.6 (-)
unnamed: D5.2 (A), R19.2
unnamed: D6.2 (A), R20.2
unnamed: J3.2, U4.2 (VIO)
unnamed: J3.3, U4.4 (CDONE)
unnamed: J3.4, U4.5 (GPIO41_RGB2)
unnamed: J3.5, U4.6 (GPIO39_RGB0)
unnamed: J3.6, U4.7 (GPIO40_RGB1)
unnamed: J3.7, U4.11 (GPIO23)
unnamed: J3.8, U4.12 (GPIO25)
unnamed: J4.4, U4.13 (GPIO26_UART_RX)
unnamed: J4.5, U4.14 (GPIO27_UART_TX)
unnamed: J5.2, U4.25 (GPIO2)
unnamed: J5.3, U4.26 (GPIO46)
unnamed: J5.4, U4.27 (GPIO47)
unnamed: J5.5, U4.28 (GPIO45)
unnamed: J5.6, U4.29 (GPIO48)
unnamed: J5.7, U4.30 (GPIO3)
unnamed: J5.8, U4.31 (GPIO4)
unnamed: J5.9, U4.32 (GPIO44_G6)
unnamed: J5.10, U4.33 (GPIO6)
unnamed: J5.11, U4.34 (GPIO9)
unnamed: J5.12, U4.35 (GPIO11)
unnamed: J5.13, U4.36 (GPIO18)
unnamed: J5.14, U4.37 (GPIO19)
unnamed: Q1.3 (D), R9.1
unnamed: Q2.3 (D), R8.1
unnamed: Q3.2 (S), Q4.2 (S)
unnamed: Q3.3 (D), R7.1
unnamed: Q4.3 (D), R10.2
unnamed: R13.2, R14.1, U2.9 (-)
unnamed: SW1.2, U4.3 (RESET)
unnamed: TP2.5, U4.18 (GPIO37_G1)
unnamed: TP2.11, U4.24 (GPIO28)
unnamed: TP3.1, U4.41 (CLK_12MHz)

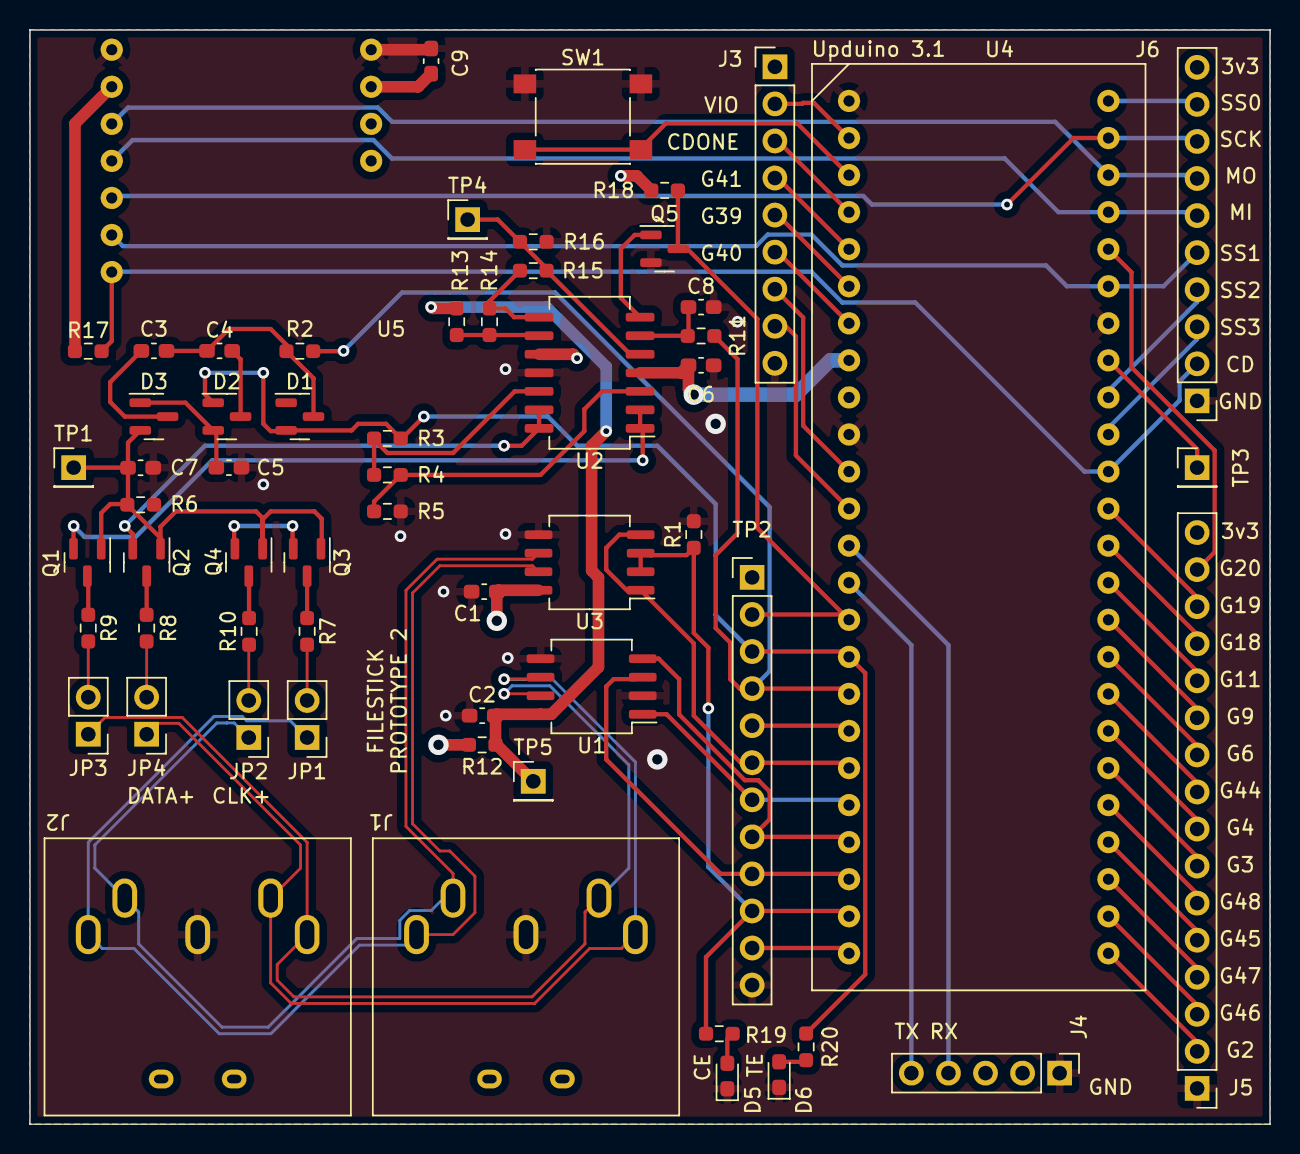
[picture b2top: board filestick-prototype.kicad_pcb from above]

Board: 4 copper layers, 85.0 x 75.0 mm, 60 parts (0 on the bottom side), 76 nets.
